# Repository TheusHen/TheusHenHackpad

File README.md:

# Hackpad (Hack Club)

A compact, four-key Hackpad built around the Seeed XIAO RP2040 with six SK6812 Mini(-E) addressable RGB LEDs and an optional I²C OLED (SSD1306). The project focuses on a clean, minimal layout with a simple 1u key grid, under-key RGB lighting, and a snug, layered case.

## Screenshots

## 3D Assembly

### Schematic

### PCB

### 3D PCB

### Case Fit

## BOM (Bill of Materials)

Download and run locally: [TheusHen/TheusHenHackpad/blob/main/BOM/ibom.html](https://github.com/TheusHen/TheusHenHackpad/blob/main/BOM/ibom.html)

## Notes

* The PCB is designed for 4 standard MX-style switches (1u each).
* Lighting uses **six** SK6812 Mini(-E) addressable RGB LEDs (daisy-chained).
* The PCB includes a **4-pin I²C OLED header** (3V3, GND, SDA, SCL) for an SSD1306-style display.
* The case image shows how the layers align and fit together.

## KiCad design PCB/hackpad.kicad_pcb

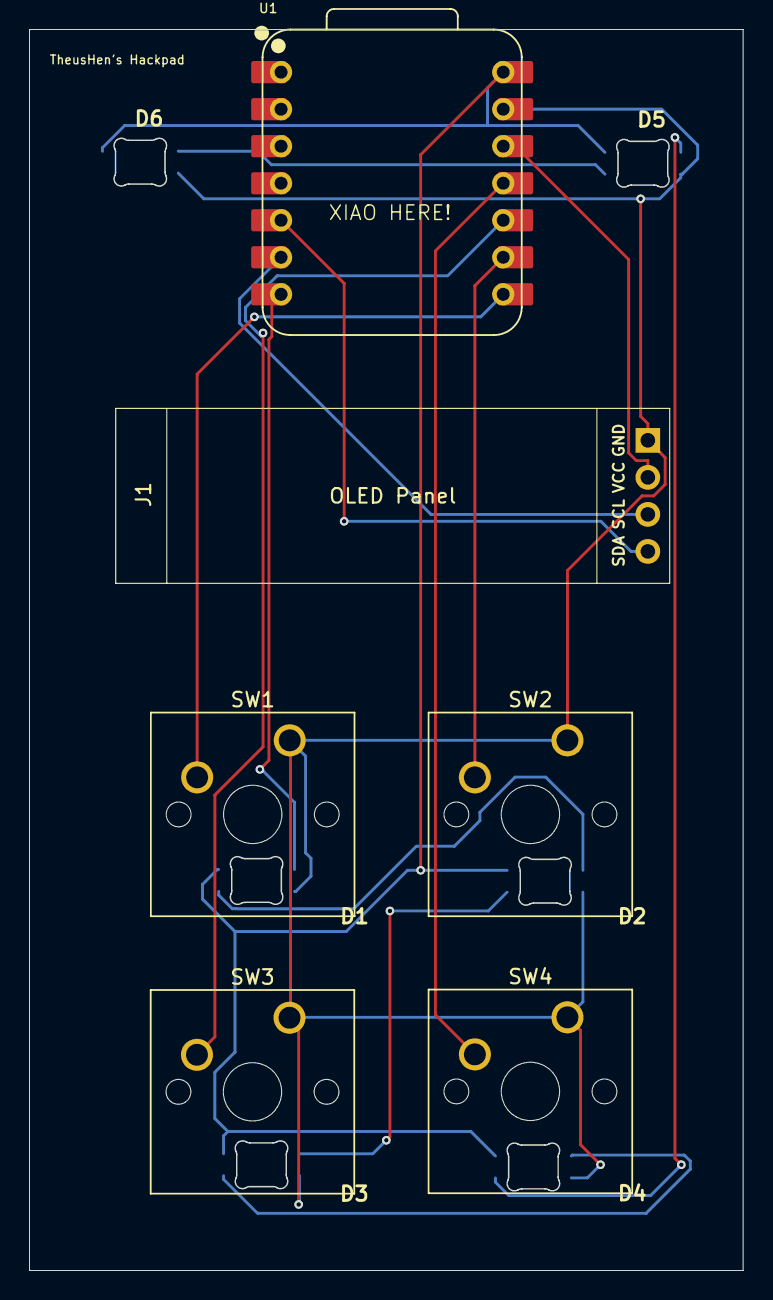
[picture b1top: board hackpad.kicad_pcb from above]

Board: 2 copper layers, 49.0 x 85.1 mm, 12 parts (0 on the bottom side), 15 nets.

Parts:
D1, D2, D3, D4, D5, D6: SK6812MINI-E; SK6812MINI-E_fixed
J1: Conn_01x04; SSD1306-0.91-OLED-4pin-128x32
SW1, SW2, SW3, SW4: SW_Push; SW_Cherry_MX_1.00u_PCB
U1: XIAO-RP2040-DIP

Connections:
3V3: J1.2, U1.12 (3V3)
+5V: D1.1 (VDD), D2.1 (VDD), D3.1 (VDD), D4.1 (VDD), D5.1 (VDD), D6.1 (VDD), U1.14 (VBUS)
GND: D1.3 (VSS), D2.3 (VSS), D3.3 (VSS), D4.3 (VSS), D5.3 (VSS), D6.3 (VSS), J1.1, SW1.1, SW2.1, SW3.1, SW4.1, U1.13 (GND)
I2C_SCL: J1.3, U1.6 (GPIO7/SCL)
I2C_SDA: J1.4, U1.5 (GPIO6/SDA)
unnamed: D1.4 (DIN), U1.7 (GPIO0/TX)
unnamed: D1.2 (DOUT), D2.4 (DIN)
unnamed: D2.2 (DOUT), D3.4 (DIN)
unnamed: D3.2 (DOUT), D4.4 (DIN)
unnamed: D4.2 (DOUT), D5.4 (DIN)
unnamed: D5.2 (DOUT), D6.4 (DIN)
unnamed: SW1.2, U1.8 (GPIO1/RX)
unnamed: SW2.2, U1.9 (GPIO2/SCK)
unnamed: SW4.2, U1.11 (GPIO3/MOSI)
unnamed: SW3.2, U1.10 (GPIO4/MISO)

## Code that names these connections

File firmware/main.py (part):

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

# Switches (per schematic):
# SW1 -> GPIO3, SW2 -> GPIO4, SW3 -> GPIO2, SW4 -> GPIO1
PIN_SW1 = pin("GP3", "D3")
PIN_SW2 = pin("GP4", "D4")
PIN_SW3 = pin("GP2", "D2")
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#   coord 3 = SW4 (bottom-right)
PINS = [PIN_SW1, PIN_SW3, PIN_SW2, PIN_SW4]

# LEDs (SK6812MINI-E) - DATA on GPIO0/TX (pin 7 on XIAO)
PIXEL_PIN = pin("GP0", "D0", "TX")
NUM_PIXELS = 6

# OLED I2C
I2C_SDA = pin("GP6", "D6")
I2C_SCL = pin("GP7", "D7")
OLED_ADDR = 0x3C
OLED_W = 128
OLED_H = 32
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
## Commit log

2026-01-21 Add firmware for KMK keyboard configuration
2026-01-21 Refactor firmware/main.py for improved functionality
2026-01-21 Refactor code structure for improved readability and maintainability
2026-01-23 Update README.md to clarify Hackpad features and specifications
2026-01-30 Add 3D assembly section with images
    Added 3D assembly images to README.
